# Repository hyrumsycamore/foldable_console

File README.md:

# foldable_console
A foldable game console that runs RetroPi on a Raspberry Pi Zero

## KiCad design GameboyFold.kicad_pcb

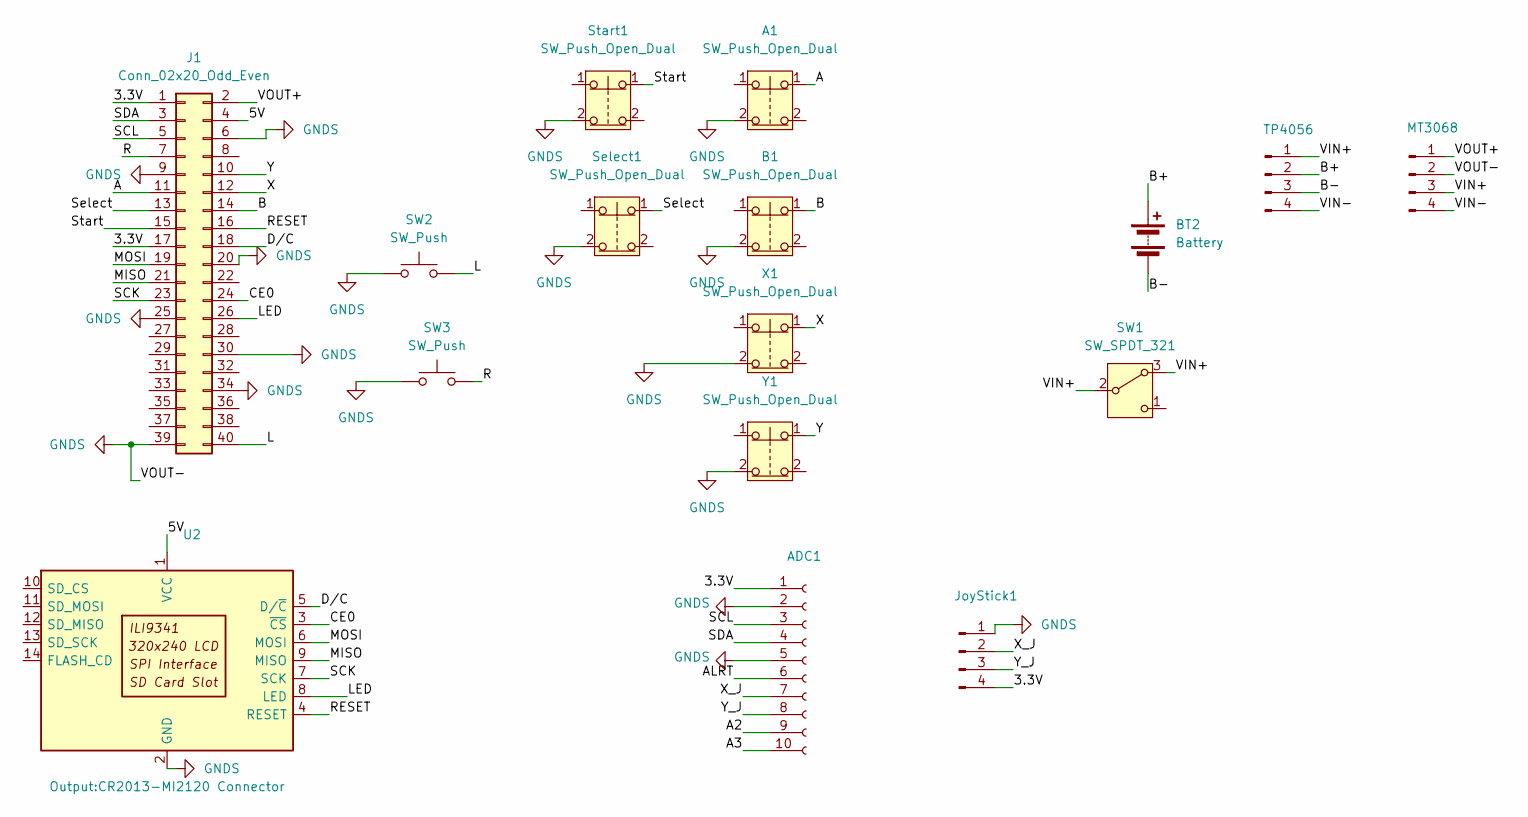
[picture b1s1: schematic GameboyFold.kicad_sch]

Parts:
A1: SW_Push_Open_Dual; Soft_Button
ADC1: Conn_01x10_Socket; ADS1115
B1: SW_Push_Open_Dual; Soft_Button
BT2: Battery; PinHeader_1x02_P2.00mm_Vertical
J1: Conn_02x20_Odd_Even; Raspberry_Pi_Zero_Socketed_THT_FaceDown_MountingHoles
JoyStick1: Conn_01x04; Joystick
MT3068: Conn_01x04_Pin; Boost Converter - MT3068
SW1: SW_SPDT_321; PinHeader_1x03_P2.54mm_Vertical
SW2, SW3: SW_Push; Sideways_button
Select1: SW_Push_Open_Dual; Soft_Button
Start1: SW_Push_Open_Dual; Soft_Button
TP4056: Conn_01x04_Pin; USB-C TP4056
U2: CR2013-MI2120; CR2013-MI2120 Connector
X1: SW_Push_Open_Dual; Soft_Button
Y1: SW_Push_Open_Dual; Soft_Button

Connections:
/3.3V: ADC1.1, J1.1, J1.17, JoyStick1.4
/5V: J1.4, U2.1 (VCC)
/A: A1.1 (2), J1.11
/A2: ADC1.9
/A3: ADC1.10
/ALRT: ADC1.6
/B: B1.1 (2), J1.14
/B+: BT2.1 (+), TP4056.2
/B-: BT2.2 (-), TP4056.3
/CE0: J1.24, U2.3 (~CS)
/D/C: J1.18, U2.5 (D/~C)
/L: J1.40, SW2.2
/LED: J1.26, U2.8 (LED)
/MISO: J1.21, U2.9 (MISO)
/MOSI: J1.19, U2.6 (MOSI)
/R: J1.7, SW3.2
/RESET: J1.16, U2.4 (RESET)
/SCK: J1.23, U2.7 (SCK)
/SCL: ADC1.3, J1.5
/SDA: ADC1.4, J1.3
/Select: J1.13, Select1.1 (2)
/Start: J1.15, Start1.1 (2)
/VIN+: MT3068.3, SW1.2 (B), SW1.3 (A), TP4056.1
/VIN-: MT3068.4, TP4056.4
/VOUT+: J1.2, MT3068.1
/X: J1.12, X1.1 (2)
/X_J: ADC1.7, JoyStick1.2
/Y: J1.10, Y1.1 (2)
/Y_J: ADC1.8, JoyStick1.3
GNDS: A1.2 (3), ADC1.2, ADC1.5, B1.2 (3), J1.6, J1.9, J1.20, J1.25, J1.30, J1.34, J1.39, JoyStick1.1, MT3068.2, SW2.1, SW3.1, Select1.2 (3), Start1.2 (3), U2.2 (GND), X1.2 (3), Y1.2 (3)

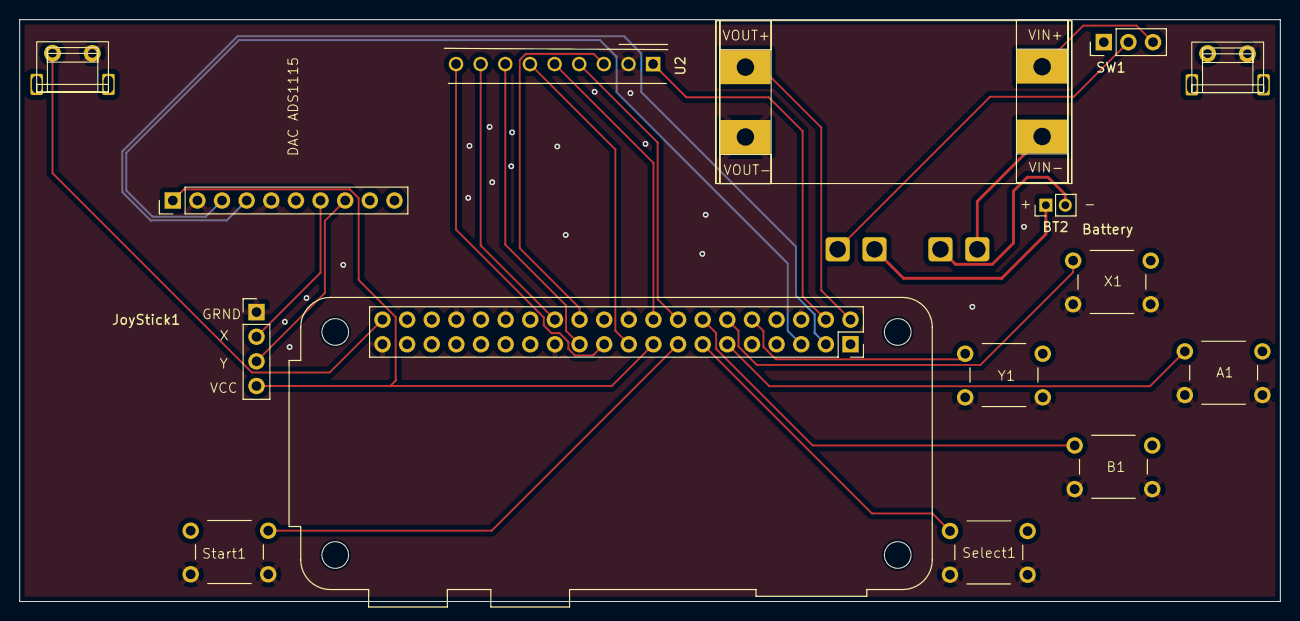
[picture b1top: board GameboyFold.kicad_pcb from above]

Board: 2 copper layers, 130.0 x 60.0 mm, 16 parts (1 on the bottom side), 27 nets.

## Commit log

2026-01-16 Sending across initial files
